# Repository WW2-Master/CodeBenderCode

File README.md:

# CodeBenderCode
THIS IS ALL OF MY CODE BENDER CODE SINCE CODE BENDER CLOSED DOWN. I DIDN'T NAZI THAT COMING!!

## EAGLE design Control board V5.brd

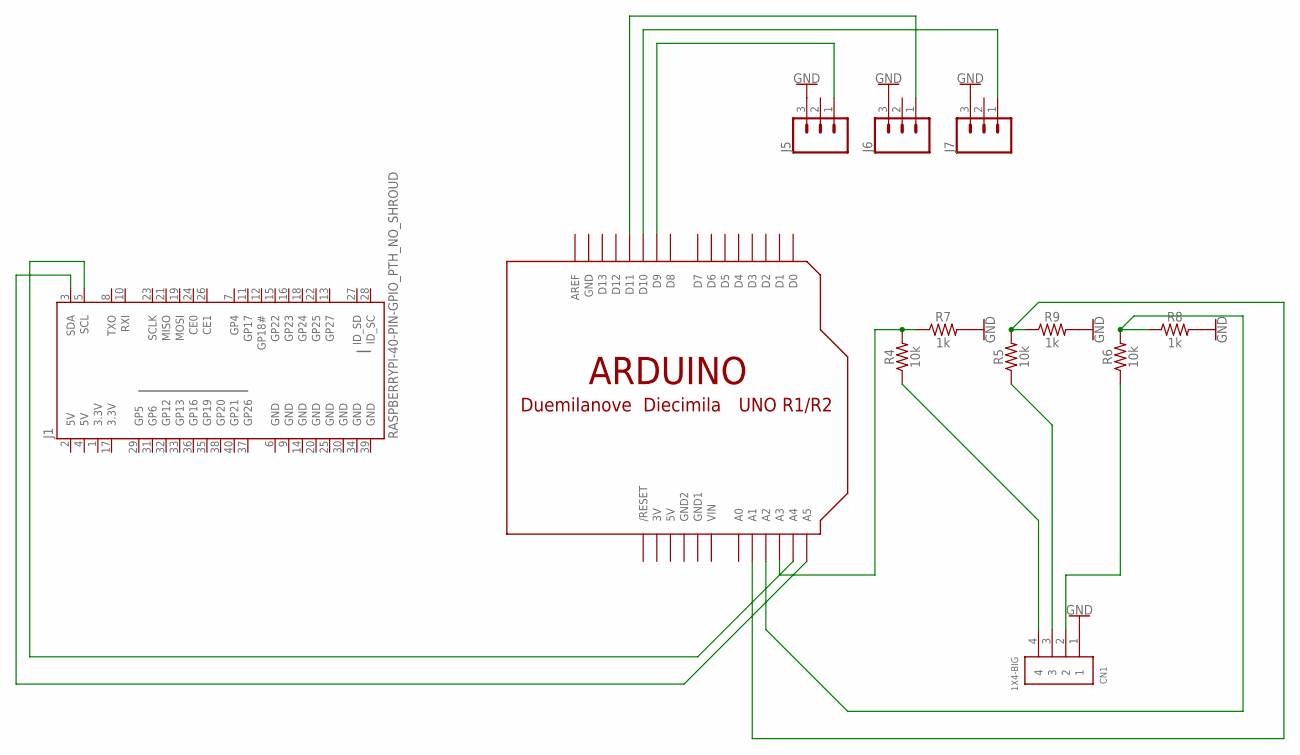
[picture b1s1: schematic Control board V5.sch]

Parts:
CN1: 1X4-BIG; 1X04-BIG
J1: RASPBERRYPI-40-PIN-GPIO_PTH_NO_SHROUD; 2X20
J5, J6, J7: CONN_03; 1X03
R4, R5, R6: 10k; AXIAL-0.3
R7, R8, R9: 1k; AXIAL-0.3
U$1: ARDUINO-BPLACE

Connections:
3.3V: J1.1 (3.3V), J1.17 (3.3V)
3V: U$1.3V
5V: J1.2 (5V), J1.4 (5V), U$1.5V
GND: CN1.1, J1.6 (GND), J1.9 (GND), J1.14 (GND), J1.20 (GND), J1.25 (GND), J1.30 (GND), J1.34 (GND), J1.39 (GND), J5.3, J6.3, J7.3, R7.P$2 (2), R8.P$2 (2), R9.P$2 (2), U$1.GND
GND1: U$1.GND1
GND2: U$1.GND2
unnamed: J1.5 (SCL), U$1.A4
unnamed: J7.1, U$1.D10
unnamed: J6.1, U$1.D11
unnamed: R4.P$2 (2), R7.P$1 (1), U$1.A3
unnamed: R6.P$2 (2), R8.P$1 (1), U$1.A2
unnamed: CN1.3, R5.P$1 (1)
unnamed: CN1.2, R6.P$1 (1)
unnamed: J5.1, U$1.D9
unnamed: J1.3 (SDA), U$1.A5
unnamed: CN1.4, R4.P$1 (1)
unnamed: R5.P$2 (2), R9.P$1 (1), U$1.A1
VIN: U$1.VIN

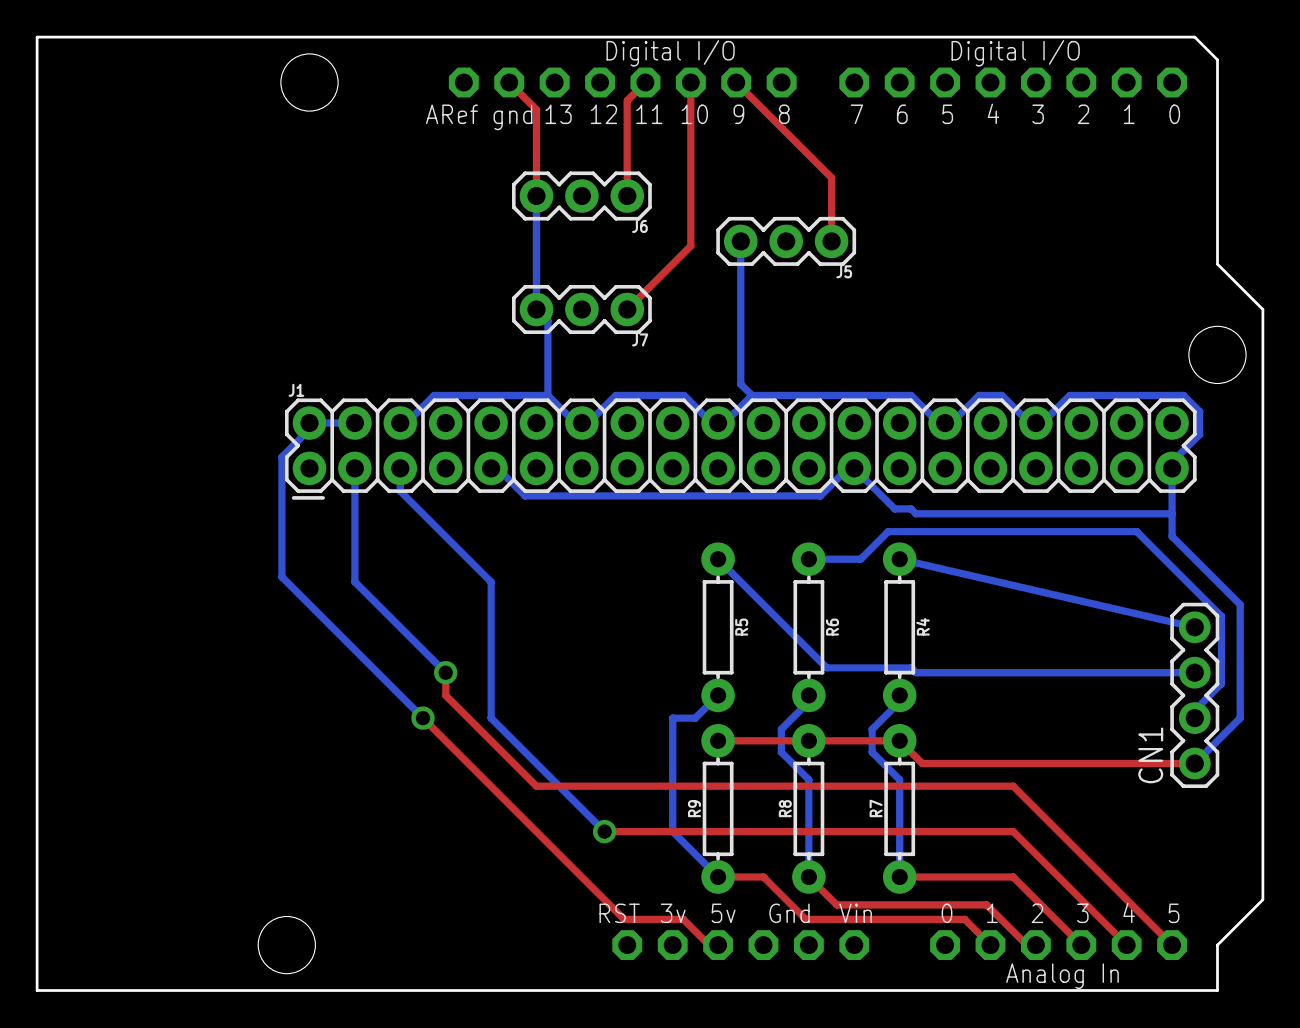
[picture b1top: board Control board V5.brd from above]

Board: 2 copper layers, 68.6 x 53.3 mm, 12 parts (0 on the bottom side), 14 nets.

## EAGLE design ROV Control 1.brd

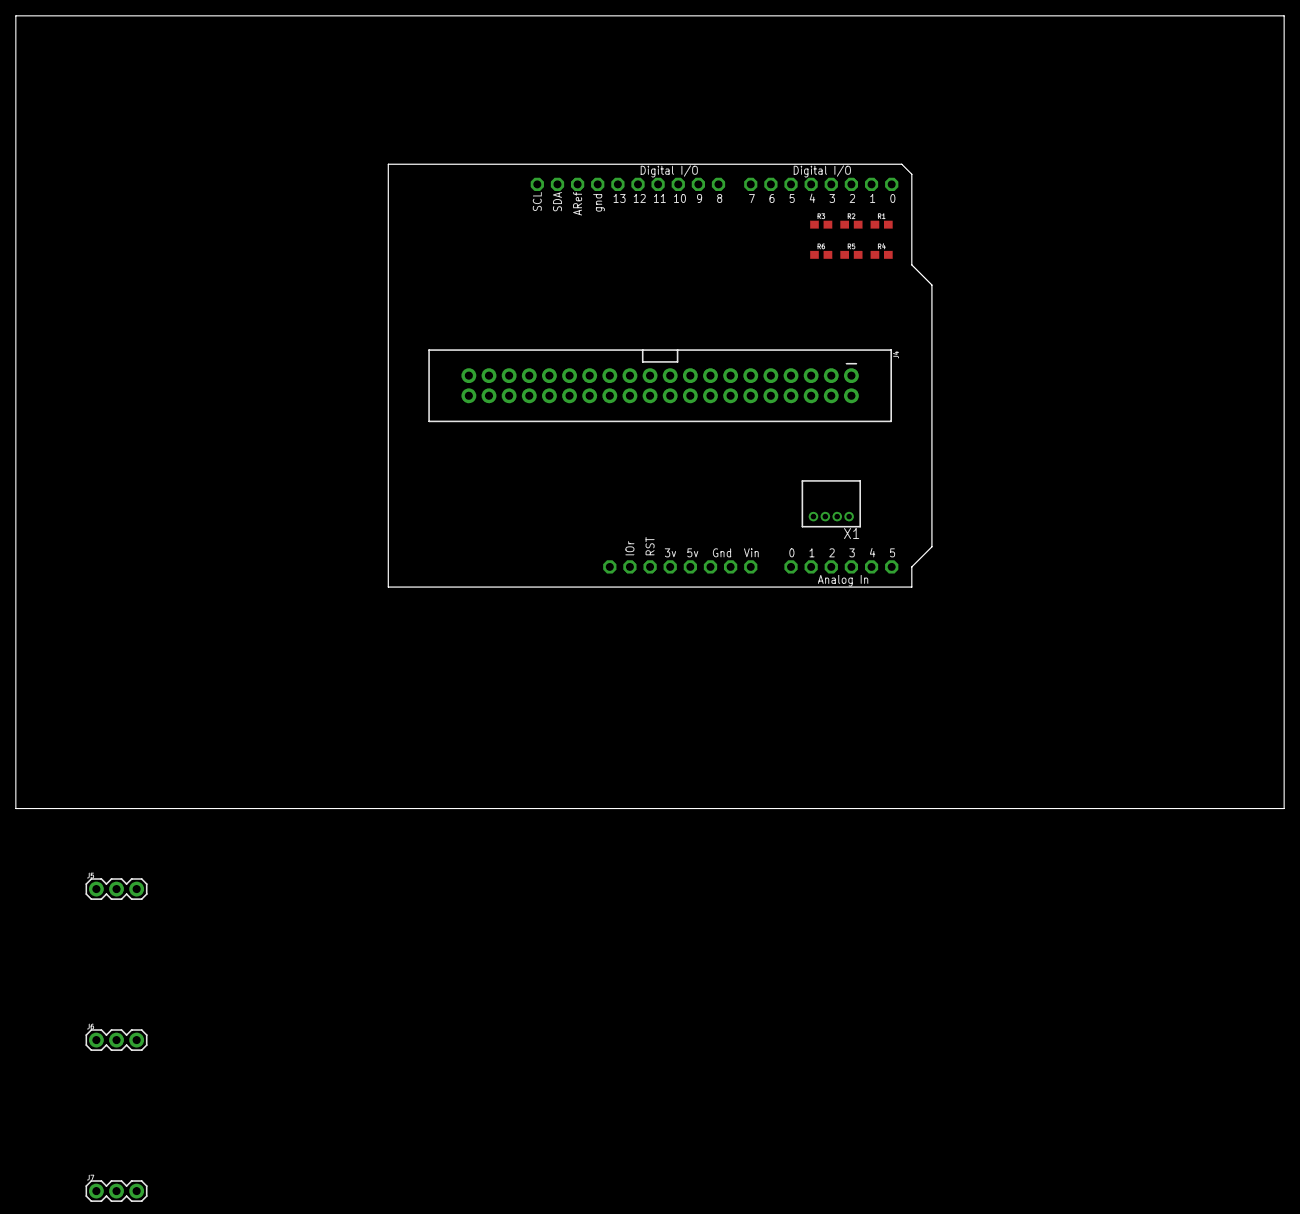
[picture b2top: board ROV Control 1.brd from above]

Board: 2 copper layers, 160.0 x 100.0 mm, 12 parts (0 on the bottom side), 13 nets, no tracks yet.

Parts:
J4: RASPBERRYPI-40-PIN-GPIO_PTH; 2X20_SHROUDED
J5, J6, J7: 1X03
R1, R2, R3: 10k; 0603
R4, R5, R6: 1k; 0603
U1: ARDUINOR3-BPLACE
X1: S4B-ZR

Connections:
3.3V: J4.1, J4.17
5V: J4.2, J4.4, U1.5V
12V: R1.1, R2.1, R3.1
GND: J4.6, J4.9, J4.14, J4.20, J4.25, J4.30, J4.34, J4.39, J5.3, J6.3, J7.3, R4.1, R5.1, R6.1, U1.GND
unnamed: U1.A1, X1.4
unnamed: J6.1, U1.D10
unnamed: J5.1, U1.D9
unnamed: J7.1, U1.D11
unnamed: U1.A2, X1.3
unnamed: U1.A3, X1.2
unnamed: R1.2, R4.2, U1.D5
unnamed: R2.2, R5.2, U1.D6
unnamed: R3.2, R6.2, U1.D7

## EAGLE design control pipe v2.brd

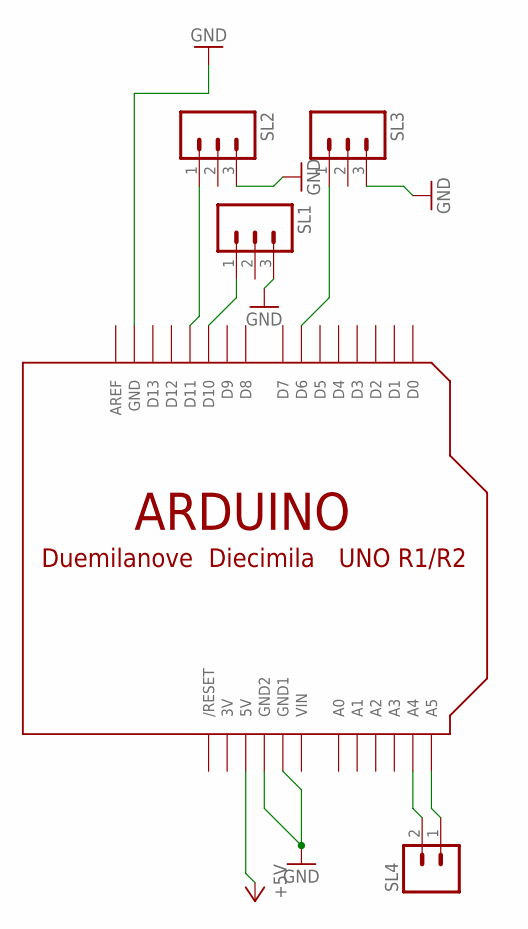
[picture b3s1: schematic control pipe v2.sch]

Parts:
SL1, SL2, SL3: M03; 03P
SL4: M02; 02P
U$1: ARDUINO-NODIM

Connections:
3V: U$1.3V
+5V: U$1.5V
GND: SL1.3, SL2.3, SL3.3, U$1.GND, U$1.GND1, U$1.GND2
unnamed: SL4.2, U$1.A4
unnamed: SL2.1, U$1.D11
unnamed: SL1.1, U$1.D10
unnamed: SL3.1, U$1.D6
unnamed: SL4.1, U$1.A5
VIN: U$1.VIN

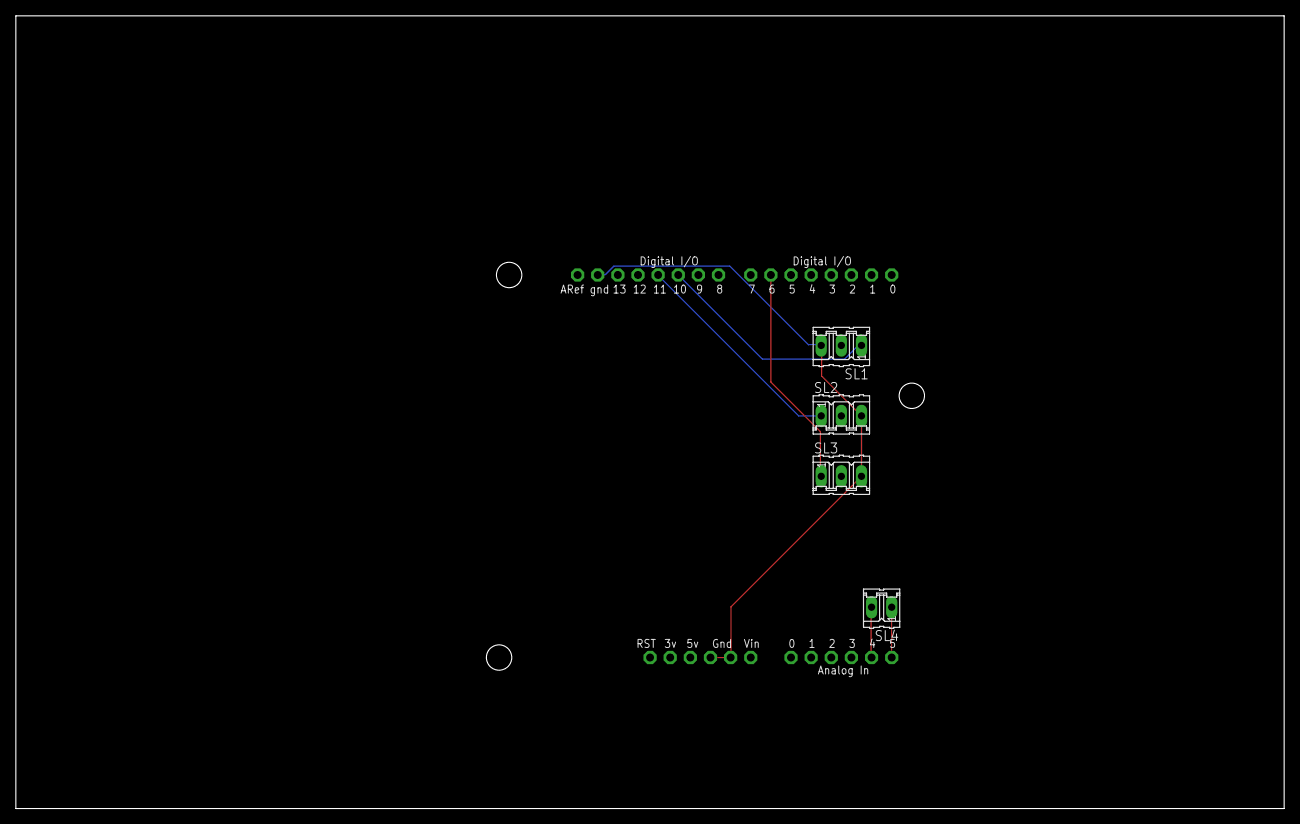
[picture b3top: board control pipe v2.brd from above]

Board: 2 copper layers, 160.0 x 100.0 mm, 5 parts (0 on the bottom side), 6 nets.

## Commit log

2016-11-01 First-GIT-thing
2017-02-02 Create ROV

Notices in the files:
parts and their libraries:
SparkFun-Connectors: Licensing: Creative Commons ShareAlike 4.0 International - https://creativecommons.org/licenses/by-sa/4.0
